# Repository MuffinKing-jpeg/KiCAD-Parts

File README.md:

# MuffinKing KiCAD components library

This is just a library of components used by me.

## TODO

- [x] Cleanup of old parts
- [x] Add list of parts

## Symbols list

### Displays

- [WeAct OLED Module 128x64](https://github.com/WeActStudio/WeActStudio.OLEDModule)

### Connectors

- PH2.0+PicoBlade1.25 THT Battery connector

### DC_DC

- TPS61022RWUR
- TPS63802DLAR
- TPS63020DSJ
- TPS63070RNM

### Diodes

#### TVS

- TPD1E10B06DPYR

### LDO

- AP7343D18FS4

### MCU

- STM32G031GxUx
- STM32G071GxUx

### PMIC

- BQ24073RGTR

## Footprints list

- UFQFPN-28
- SOT-523
- Molex PicoBlade 1x3 THT

### Reduced silk

- Header P1.27 1x03
- Header P1.27 1x05

### TI Specific abomination

- RGT16 (VQFN-16)
- RWU0007A (VQFN-7)
- X1SON-2 (0402 ***WTF, TI???***)
- X2SON-4
- DLA0010A (VSON-HR 10pin)
- DSJ14
- RNM0015A

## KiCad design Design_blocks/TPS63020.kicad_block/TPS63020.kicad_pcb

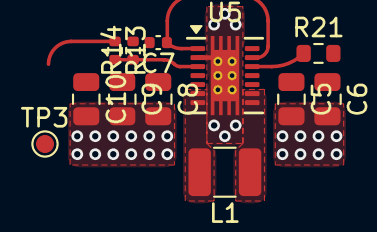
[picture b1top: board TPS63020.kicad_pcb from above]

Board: 4 copper layers, 12 parts (0 on the bottom side), 8 nets.

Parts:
C5, C6, C8, C9, C10: 22u; C_0805_2012Metric
C7: 0.1u; C_0402_1005Metric
L1: 1.5u; L_1210_3225Metric
R13: 1M; R_0402_1005Metric
R14: 180k; R_0402_1005Metric
R21: 10k; R_0603_1608Metric
TP3: 3V3; TestPoint_Pad_D1.0mm
U5: TPS63020DSJR; DSJ14_2P85X1P58

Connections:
+3V3: C8.1, C9.1, C10.1, R13.1, TP3.1 (1_1), U5.4 (VOUT), U5.5 (VOUT)
/en: R21.1, U5.12 (EN)
GND: C5.2, C6.2, C7.2, C8.2, C9.2, C10.2, R14.2, U5.2 (GND), U5.15 (EPAD)
unnamed: L1.1, U5.8 (L1), U5.9 (L1)
unnamed: L1.2, U5.6 (L2), U5.7 (L2)
unnamed: R13.2, R14.1, U5.3 (FB)
unnamed: C7.1, U5.1 (VINA), U5.13 (PS/SYNC)
VSYS: C5.1, C6.1, R21.2, U5.10 (VIN), U5.11 (VIN)

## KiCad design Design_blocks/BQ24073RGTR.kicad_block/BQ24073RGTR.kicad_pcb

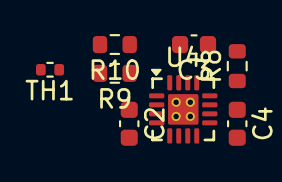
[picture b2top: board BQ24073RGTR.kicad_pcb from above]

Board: 4 copper layers, 8 parts (0 on the bottom side), 8 nets, no tracks yet.

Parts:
C2, C4: 4.7u; C_0603_1608Metric
C3: 1u; C_0603_1608Metric
R8: 1.1k; R_0603_1608Metric
R9: 33k; R_0603_1608Metric
R10: 3.3k; R_0603_1608Metric
TH1: 10k NTC; R_0402_1005Metric
U4: BQ24073RGTR; RGT16

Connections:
/power/VBAT: C2.1, U4.2 (BAT), U4.3 (BAT)
/power/VBUS: C3.1, U4.13 (IN)
GND: C2.2, C3.2, C4.2, R8.2, R9.2, R10.2, TH1.2, U4.4 (*CE), U4.6 (EN1), U4.8 (VSS), U4.15 (TD), U4.17 (EPAD)
unnamed: R8.1, U4.12 (ILIM)
unnamed: R10.1, U4.16 (ISET)
unnamed: R9.1, U4.14 (TMR)
unnamed: TH1.1, U4.1 (TS)
VSYS: C4.1, U4.5 (EN2), U4.10 (OUT), U4.11 (OUT)

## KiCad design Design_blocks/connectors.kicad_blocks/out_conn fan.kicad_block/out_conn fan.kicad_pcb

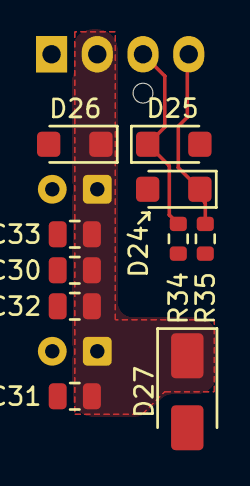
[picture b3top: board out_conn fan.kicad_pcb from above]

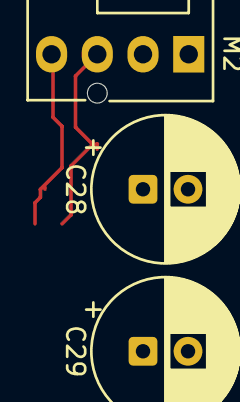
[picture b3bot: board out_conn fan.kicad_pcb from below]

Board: 4 copper layers, 13 parts (3 on the bottom side), 4 nets.

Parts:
C28, C29: 220uF; CP_Radial_D8.0mm_P2.50mm
C30, C31, C32, C33: 22u; C_0805_2012Metric
D24, D25, D26: SMF15A; D_SMF
D27: SS34; D_SMA
M2: Fan_4pin; FanPinHeader_1x04_P2.54mm_Vertical
R34, R35: 100; R_0603_1608Metric

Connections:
/Connectors/out_conn fan1/PWM_IN: D24.1 (A1), M2.4 (PWM), R35.1
/Connectors/out_conn fan1/RPM_IN: D25.1 (A1), M2.3 (Tacho), R34.1
/Connectors/out_conn fan1/VCONN: C28.1, C29.1, C30.1, C31.1, C32.1, C33.1, D26.1 (A1), D27.1 (K), M2.2 (+)
GND: C28.2, C29.2, C30.2, C31.2, C32.2, C33.2, D24.2 (A2), D25.2 (A2), D26.2 (A2), M2.1 (-)

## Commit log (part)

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2025-09-13 Moved fotprints to one file
2025-09-13 Moved symbols to categories
2025-09-14 Added 3d models
2025-09-14 Added todo in readme
2025-09-15 Fixed path for 3D models. Added TPS61022RWUR
2025-09-15 Fixed polygons for connector
2025-09-16 Added footprint for JST 1x3 P1.25
2025-09-16 Updated connectors
2025-09-17 Fixed SW pin type for ERC checks
2025-09-18 Updated reference field
2025-09-21 Removed old and replaced components
2025-10-05 Added 128x64 OLED Display module
2025-10-07 Added new parts - STM32G071GxU - TPS63020DSJ - TPS63070RNM - WeAct OLED 128x64
2025-10-07 Added back designators to silk layer
2025-10-12 Updated position of reference names
2025-12-14 Added MSK12C02 slider
2025-12-14 Added custom picoblade (3p & 5p) connectors
2025-12-14 Added custom PH2.0 connector
2025-12-28 Added symbols for SMT picoblade connectors
2025-12-28 Added new side button
2026-04-09 Fixed 3d for TPS63020
2026-04-09 Added lib for debug connectors
2026-04-11 added footprint for debug clip 7p
2026-04-26 Updated TPD1E1 symbol
2026-04-26 Added design block for TPS63020 and BQ24073
2026-04-26 Add design blocks for fan connectors, OPA2188 with shunts, pwm controlled mosfet.
2026-04-30 Updated EDGE connector for USB-A
2026-05-02 Added BQ24040DSQR
2026-05-23 Tweaked design blocks for BQ24073 and TPS63020
2026-05-23 Added abomination of footprint to use LTST-C19HE1WT upside down
2026-05-23 Added footprint for Kalih Choc with cutout for LED
2026-06-01 Updated design block for tps63020
2026-06-02 Fixed keepout area
